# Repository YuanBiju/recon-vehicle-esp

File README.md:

## Navigate
The Kicad files are in Hardware/PCB_Design
## Resources
Getting familiar with Kicad: [Blinky 5.0](https://www.youtube.com/watch?v=-7yFlz6wdUA&list=PLy2022BX6EspFAKBCgRuEuzapuz_4aJCn&index=5)</br>
ESP32-CAM 3d model: https://3dmixers.com/m/235949-esp32cam-kicad-3d-model</br>
L298N 3d model: https://www.snapeda.com/parts/L298N/STMicroelectronics/view-part/

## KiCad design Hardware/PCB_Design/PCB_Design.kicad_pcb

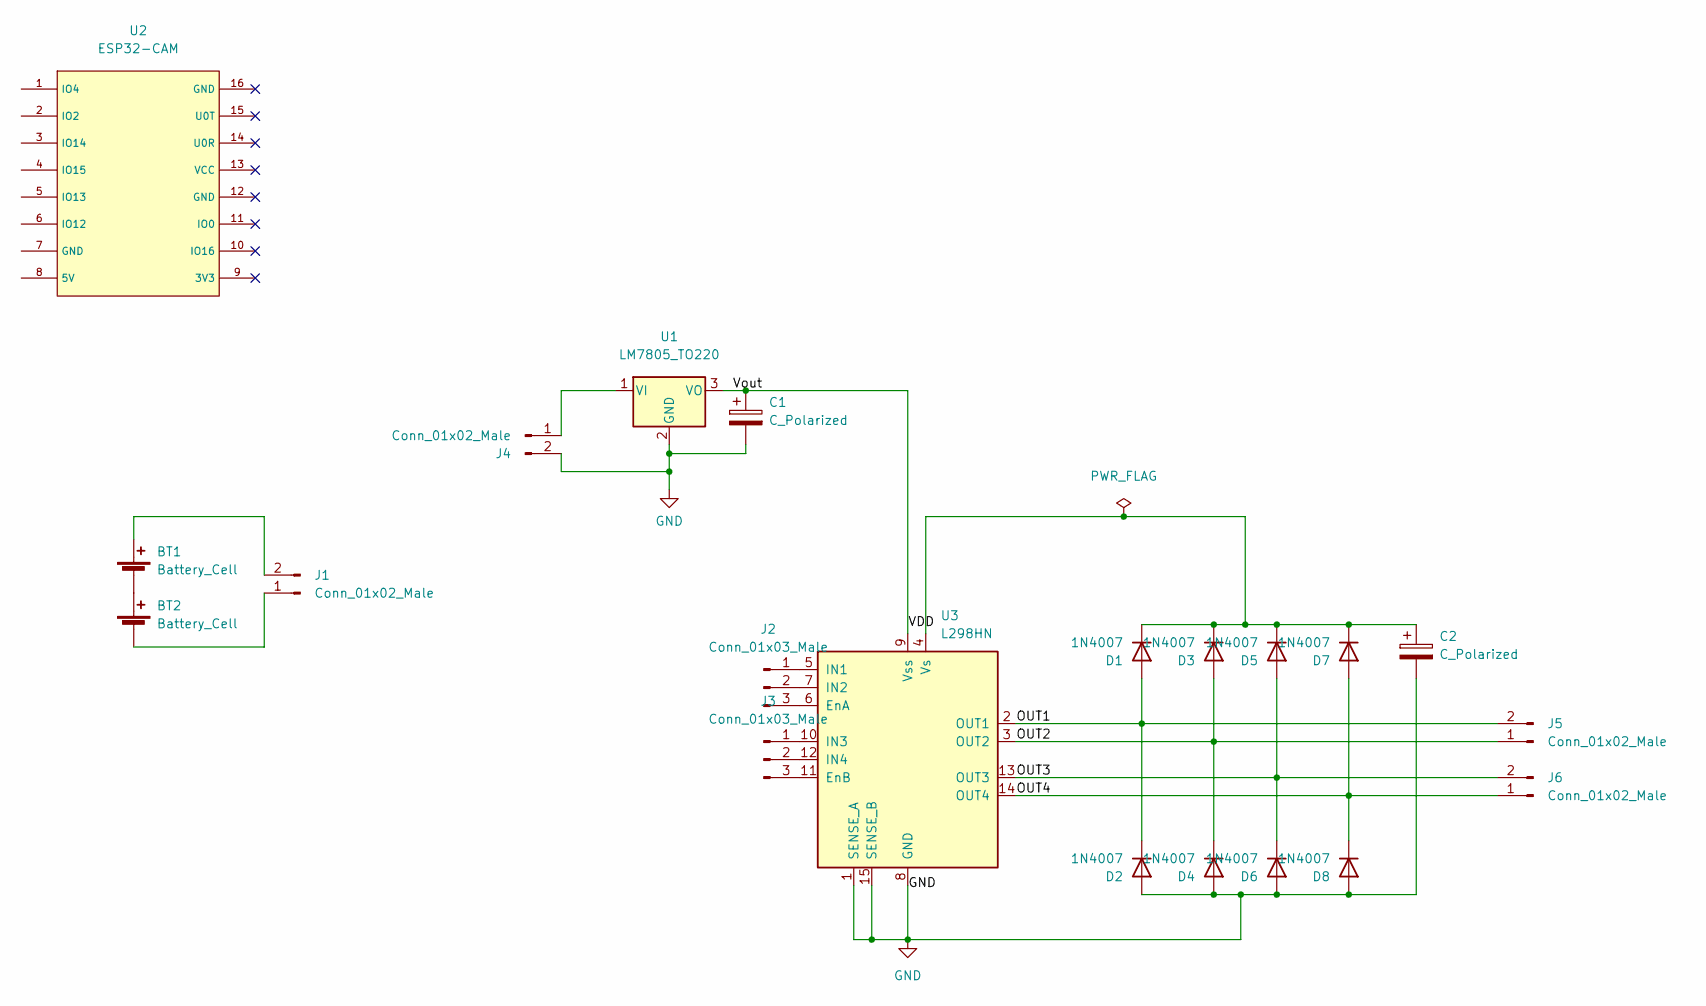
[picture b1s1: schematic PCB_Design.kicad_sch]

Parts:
BT1, BT2: Battery_Cell; BatteryHolder_MPD_BH-18650-PC2
C1, C2: C_Polarized; CP_Elec_3x5.3
D1, D2, D3, D4, D5, D6, D7, D8: 1N4007; D_DO-41_SOD81_P10.16mm_Horizontal
J1, J4, J5, J6: Conn_01x02_Male; PinHeader_1x02_P1.00mm_Vertical
J2, J3: Conn_01x03_Male; PinHeader_1x03_P1.00mm_Vertical
U1: LM7805_TO220; TO-220-3_Vertical
U2: ESP32-CAM
U3: L298HN; L298N

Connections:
/OUT1: D1.2 (A), D2.1 (K), J5.2, U3.2 (OUT1)
/OUT2: D3.2 (A), D4.1 (K), J5.1, U3.3 (OUT2)
/OUT3: D5.2 (A), D6.1 (K), J6.2, U3.13 (OUT3)
/OUT4: D7.2 (A), D8.1 (K), J6.1, U3.14 (OUT4)
/VDD: C1.1, U1.3 (VO), U3.9 (Vss)
GND: C1.2, C2.2, D2.2 (A), D4.2 (A), D6.2 (A), D8.2 (A), J4.2, U1.2 (GND), U3.1 (SENSE_A), U3.8 (GND), U3.15 (SENSE_B)
unnamed: BT1.1 (+), J1.2
unnamed: BT1.2 (-), BT2.1 (+)
unnamed: C2.1, D1.1 (K), D3.1 (K), D5.1 (K), D7.1 (K), U3.4 (Vs)
unnamed: BT2.2 (-), J1.1
unnamed: J2.1, U3.5 (IN1)
unnamed: J2.2, U3.7 (IN2)
unnamed: J2.3, U3.6 (EnA)
unnamed: J3.1, U3.10 (IN3)
unnamed: J3.2, U3.12 (IN4)
unnamed: J3.3, U3.11 (EnB)
unnamed: J4.1, U1.1 (VI)

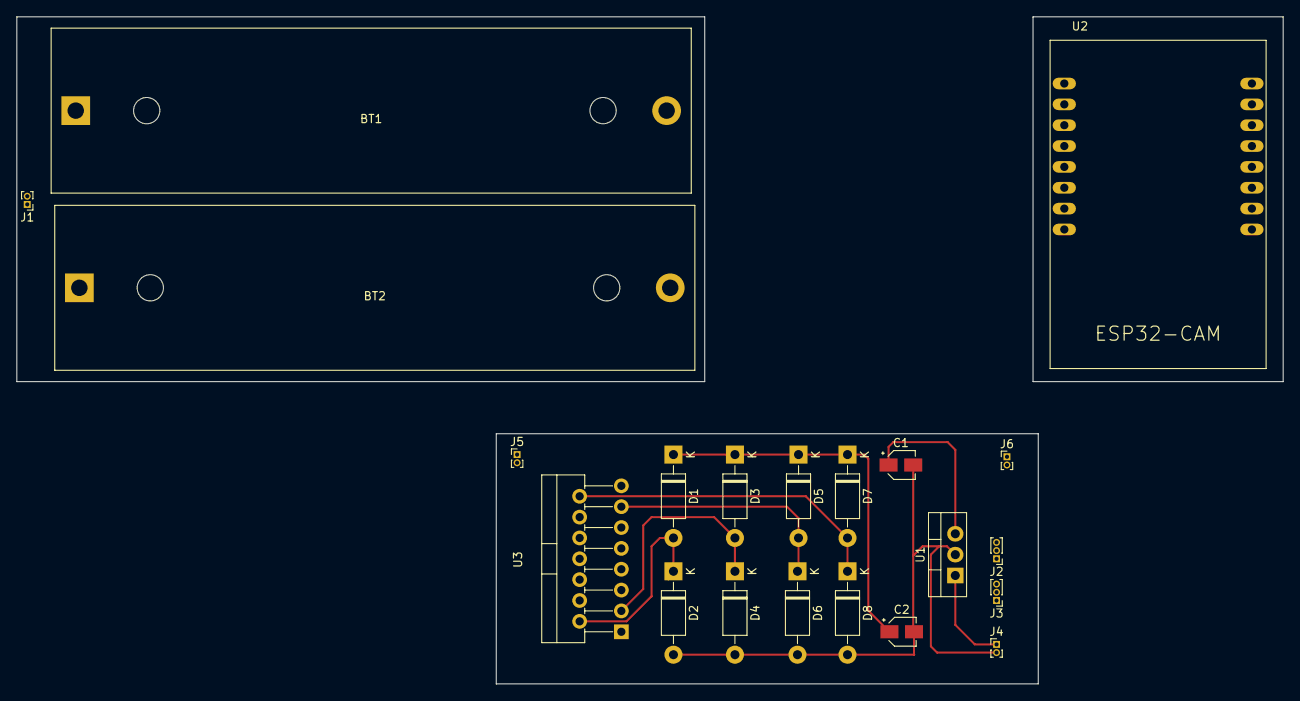
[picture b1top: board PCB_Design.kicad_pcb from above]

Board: 2 copper layers, 154.3 x 81.3 mm, 21 parts (0 on the bottom side), 17 nets.

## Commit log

2022-05-03 first commit; contains bare files
2022-05-04 added initial rough schematic; added required libraries; updated pcb
2022-05-05 added esp32-cam 3d-model; updated pcb design
2022-05-05 added readme file
2022-07-03 updated pcb and schematic;added header connectors;did some routing
2022-07-03 renamed project
